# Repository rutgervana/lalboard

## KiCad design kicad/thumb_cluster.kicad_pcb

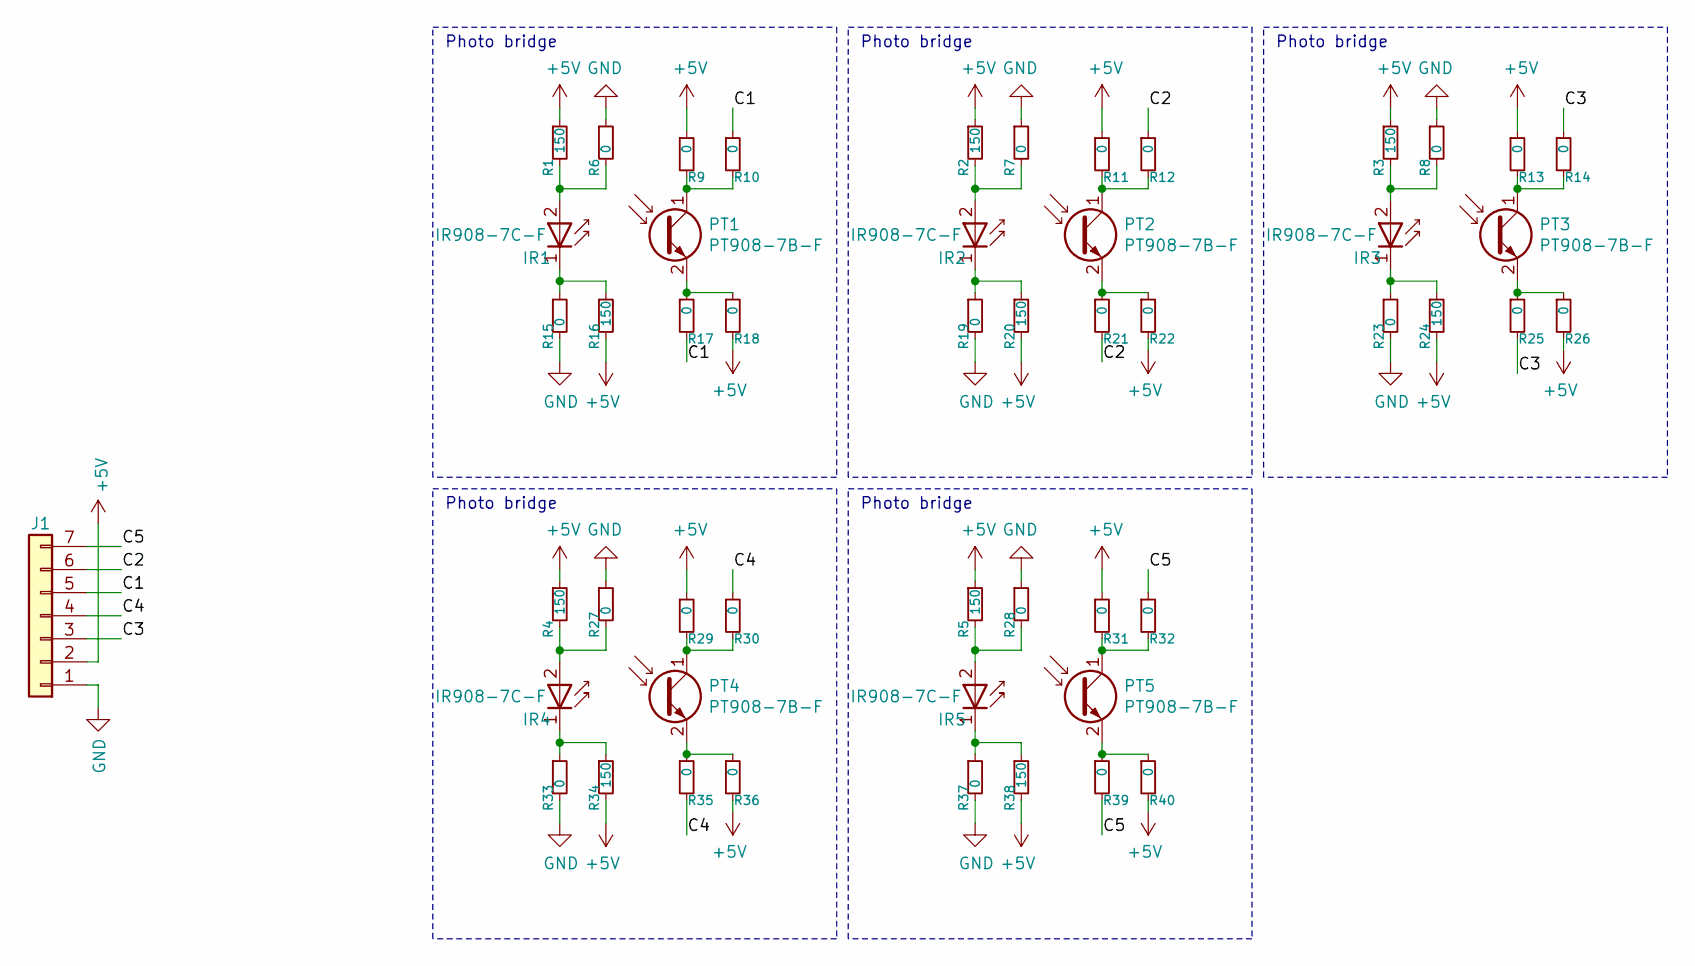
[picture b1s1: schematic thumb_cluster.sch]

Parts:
IR1, IR2, IR3, IR4, IR5: IR908-7C-F
J1: Conn_01x07; JST_ZH_B7B-ZR_1x07_P1.50mm_Vertical
PT1, PT2, PT3, PT4, PT5: PT908-7B-F; PT908-7C-F
R1, R2, R3, R4, R5, R16, R20, R24, R34, R38: 150; R_0603_1608Metric
R6, R7, R8, R9, R10, R11, R12, R13, R14, R15, R17, R18, R19, R21, R22, R23, R25, R26, R27, R28, R29, R30, R31, R32, R33, R35, R36, R37, R39, R40: 0; R_0603_1608Metric

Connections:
+5V: J1.2, R1.1, R2.1, R3.1, R4.1, R5.1, R9.1, R11.1, R13.1, R16.2, R18.2, R20.2, R22.2, R24.2, R26.2, R29.1, R31.1, R34.2, R36.2, R38.2, R40.2
/C1: J1.5, R10.1, R17.2
/C2: J1.6, R12.1, R21.2
/C3: J1.3, R14.1, R25.2
/C4: J1.4, R30.1, R35.2
/C5: J1.7, R32.1, R39.2
GND: J1.1, R6.1, R7.1, R8.1, R15.2, R19.2, R23.2, R27.1, R28.1, R33.2, R37.2
unnamed: IR1.1 (K), R15.1, R16.1
unnamed: IR1.2 (A), R1.2, R6.2
unnamed: IR2.1 (K), R19.1, R20.1
unnamed: IR2.2 (A), R2.2, R7.2
unnamed: IR3.1 (K), R23.1, R24.1
unnamed: IR3.2 (A), R3.2, R8.2
unnamed: IR4.1 (K), R33.1, R34.1
unnamed: IR4.2 (A), R4.2, R27.2
unnamed: IR5.1 (K), R37.1, R38.1
unnamed: IR5.2 (A), R5.2, R28.2
unnamed: PT1.1 (C), R9.2, R10.2
unnamed: PT1.2 (E), R17.1, R18.1
unnamed: PT2.1 (C), R11.2, R12.2
unnamed: PT2.2 (E), R21.1, R22.1
unnamed: PT3.1 (C), R13.2, R14.2
unnamed: PT3.2 (E), R25.1, R26.1
unnamed: PT4.1 (C), R29.2, R30.2
unnamed: PT4.2 (E), R35.1, R36.1
unnamed: PT5.1 (C), R31.2, R32.2
unnamed: PT5.2 (E), R39.1, R40.1

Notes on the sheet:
Photo bridge

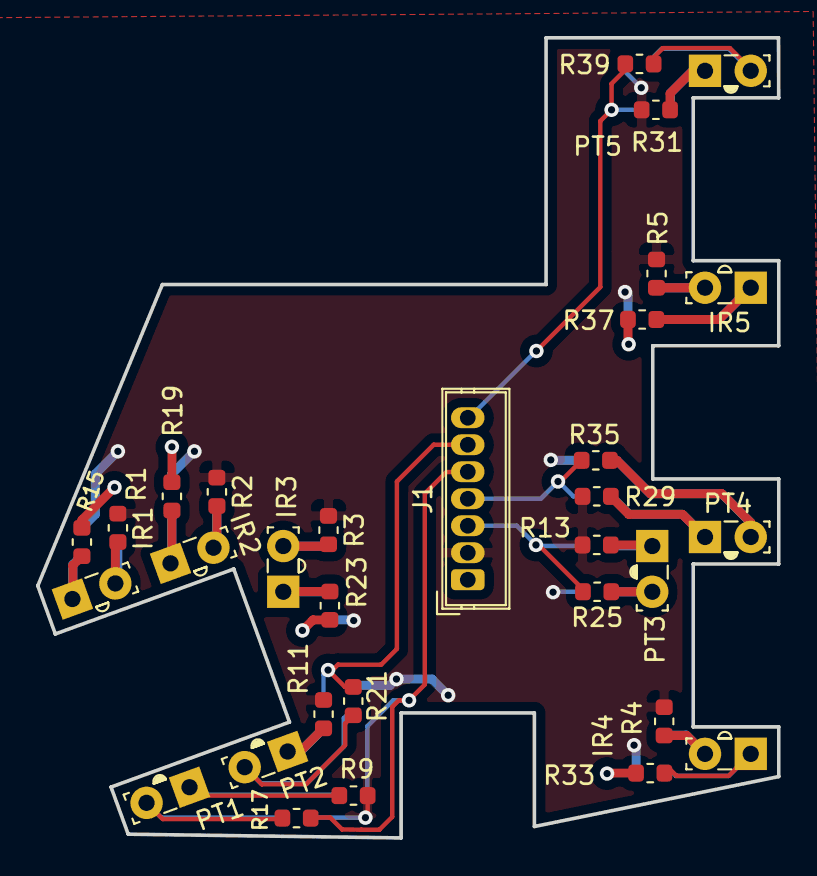
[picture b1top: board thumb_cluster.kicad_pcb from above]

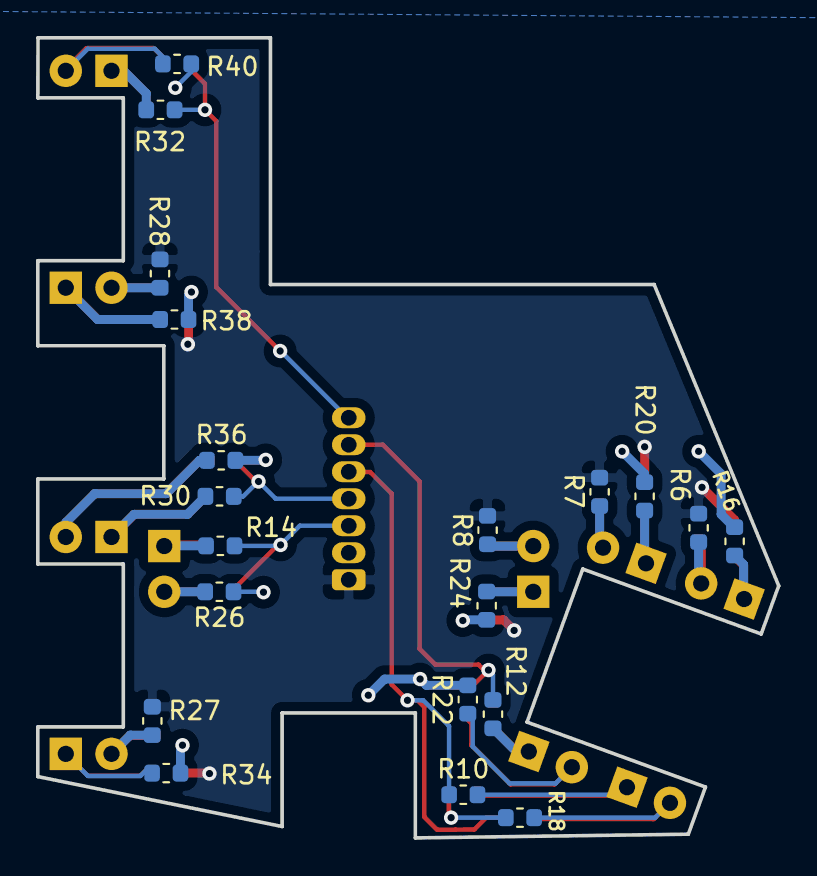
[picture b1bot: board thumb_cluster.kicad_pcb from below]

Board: 2 copper layers, 41.2 x 44.5 mm, 51 parts (20 on the bottom side), 27 nets.

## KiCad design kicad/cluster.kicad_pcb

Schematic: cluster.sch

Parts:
IR1, IR2, IR3, IR4, IR5: IR908-7C-F
J1: Conn_01x07; JST_ZH_S7B-ZR_1x07_P1.50mm_Horizontal
PT1, PT2, PT3, PT4, PT5: PT908-7B-F; PT908-7C-F
R1, R2, R3, R4, R5: 150; R_0603_1608Metric

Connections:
+5V: IR1.2 (A), IR2.2 (A), IR3.2 (A), IR4.2 (A), IR5.2 (A), J1.2, PT1.2, PT2.2, PT3.2, PT4.2, PT5.2
C1: J1.1, PT1.1
C3: J1.3, PT2.1
C4: J1.4, PT3.1
C5: J1.5, PT4.1
C6: J1.6, PT5.1
GND: J1.7, R1.1, R2.1, R3.1, R4.1, R5.1
unnamed: IR1.1 (K), R1.2
unnamed: IR2.1 (K), R2.2
unnamed: IR3.1 (K), R3.2
unnamed: IR4.1 (K), R4.2
unnamed: IR5.1 (K), R5.2

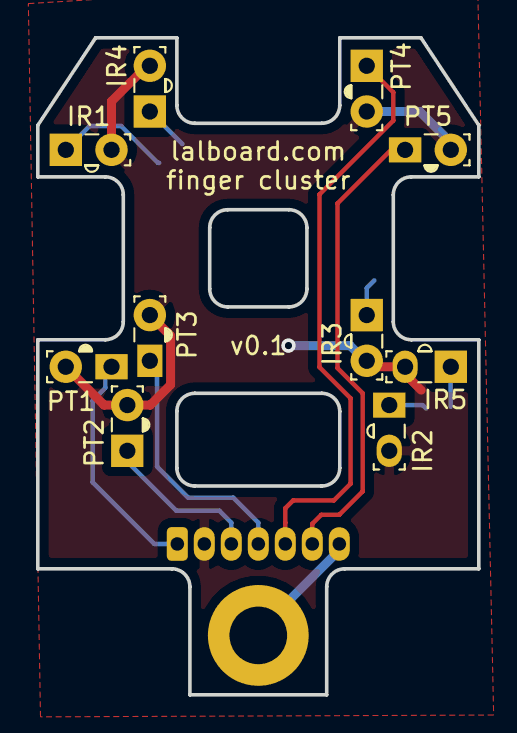
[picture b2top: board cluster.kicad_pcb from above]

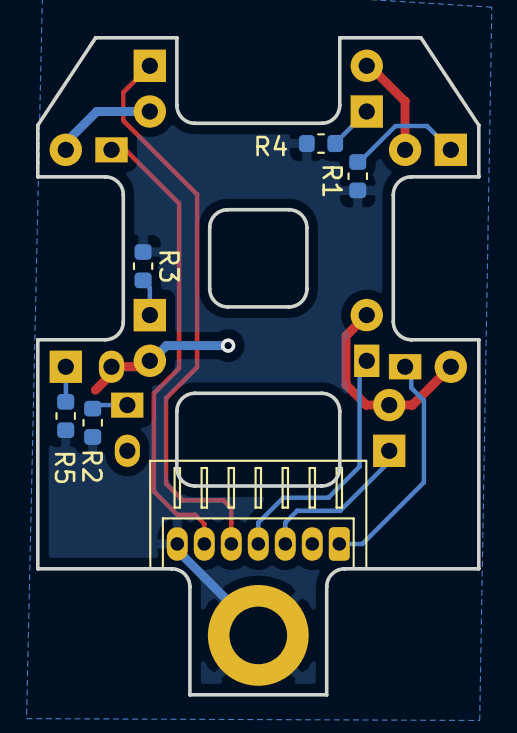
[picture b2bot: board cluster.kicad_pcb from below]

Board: 2 copper layers, 24.5 x 36.5 mm, 16 parts (6 on the bottom side), 12 nets.

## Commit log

2021-03-16 Added ground planes, combined left and right thumb cluster PCBs
